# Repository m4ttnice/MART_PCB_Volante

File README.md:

# MART_PCB_Volante
PCB (Nano ucontroller based) that manages Inputs for the "MART_Pi" design.

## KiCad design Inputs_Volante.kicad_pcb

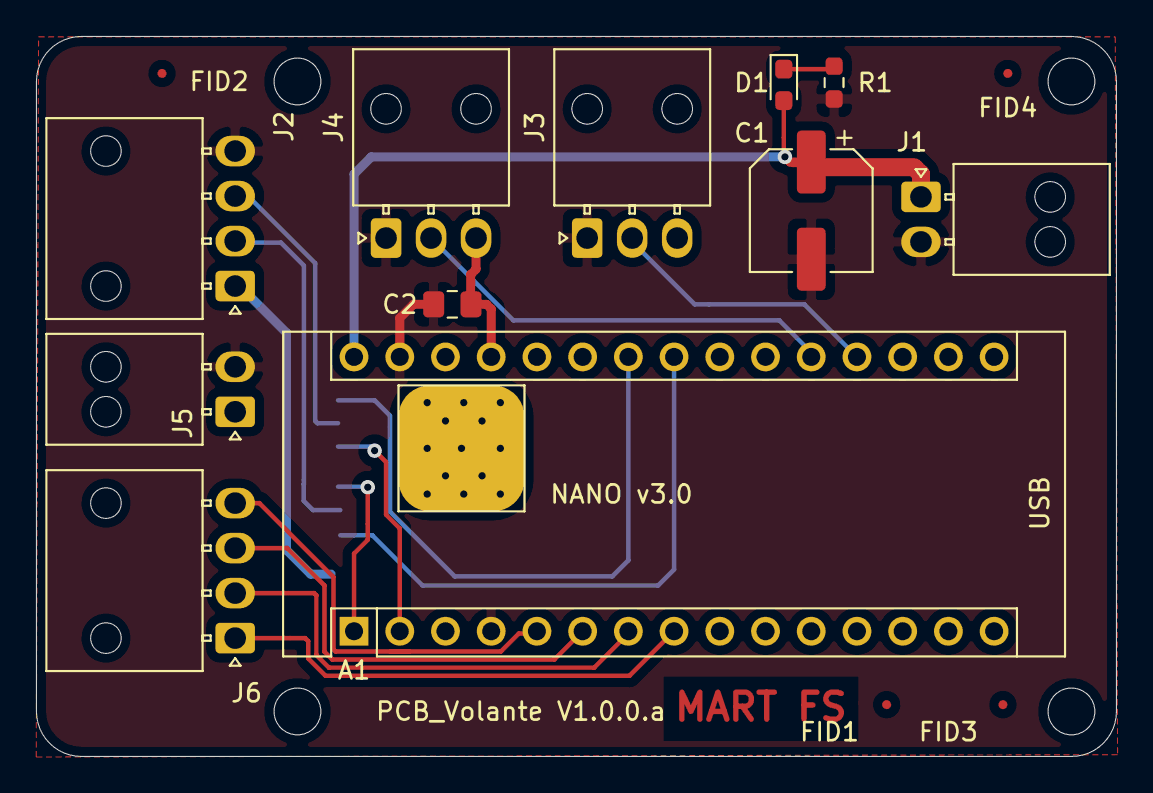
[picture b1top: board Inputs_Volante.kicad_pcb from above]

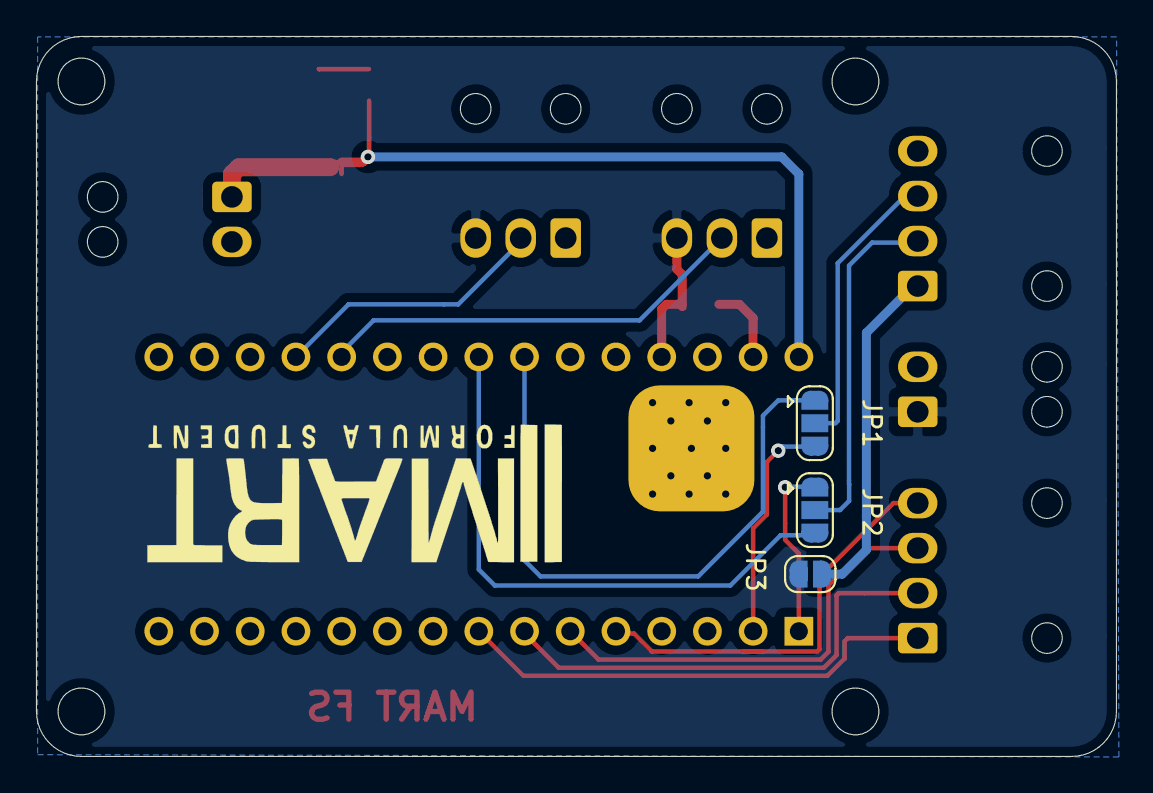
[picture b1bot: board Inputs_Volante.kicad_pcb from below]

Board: 2 copper layers, 60.0 x 40.0 mm, 19 parts (3 on the bottom side), 17 nets.

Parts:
 : ThermalPad07_07
A1: Arduino_Nano_v3.x; Arduino_Nano
C1: CP; CP_Elec_6.3x7.7
C2: C; C_0805_2012Metric_Pad1.18x1.45mm_HandSolder
D1: G-LED; LED_0603_1608Metric_Pad1.05x0.95mm_HandSolder
FID1, FID2, FID3: Fiducial; Fiducial_0.5mm_Mask1.5mm
FID4: Fid; Fiducial_0.5mm_Mask1.5mm
J1: 01x02_PowSupply; Molex_Nano-Fit_105313-xx02_1x02_P2.50mm_Horizontal
J2: 01x04_BtnSignal; Molex_Nano-Fit_105313-xx04_1x04_P2.50mm_Horizontal
J3: 01x03_Enco0; Molex_Nano-Fit_105313-xx03_1x03_P2.50mm_Horizontal
J4: 01x03_Enco1; Molex_Nano-Fit_105313-xx03_1x03_P2.50mm_Horizontal
J5: 01x02_BtnSupply; Molex_Nano-Fit_105313-xx02_1x02_P2.50mm_Horizontal
J6: 01x04_Comm; Molex_Nano-Fit_105313-xx04_1x04_P2.50mm_Horizontal
JP1, JP2: SolderJumper_3_Open; SolderJumper-3_P1.3mm_Open_RoundedPad1.0x1.5mm
JP3: SolderJumper_2_Open; SolderJumper-2_P1.3mm_Open_RoundedPad1.0x1.5mm
R1: R_Small; R_0603_1608Metric_Pad0.98x0.95mm_HandSolder

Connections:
+12V: A1.30, C1.1, D1.2, J1.1
Btn0: A1.5, J6.4
Btn1: A1.6, J6.3
Btn2: A1.7, J6.2
Btn3: A1.8, J6.1
Enco0_D: A1.19, J3.2
Enco1_D: A1.20, J4.2
GND: A1.4, A1.29, C1.2, C2.1, J1.2, J2.4, J3.1, J4.1, J5.2, R1.2
unnamed: D1.1, R1.1
unnamed: J2.1, JP3.2
unnamed: J2.2, JP2.2
unnamed: J2.3, JP1.2
RX: A1.2, JP1.3
SCL: A1.24, JP1.1
SDA: A1.23, JP2.3
TX: A1.1, JP2.1
VCC: A1.27, C2.2, J3.3, J4.3, J5.1, JP3.1

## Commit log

2021-05-07 PCB Volante para el proyecto MART-Pi
2021-05-07 Add schematics to README.md
2021-10-29 Create LICENSE
    CC-BY-SA-4.0
2021-10-29 Create MART_20-21_Project
